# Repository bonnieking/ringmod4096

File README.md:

# ringmod4096

Simple and cool audio effects.

Adapted from:

https://www.asciipr0n.com/4096/ringmod/

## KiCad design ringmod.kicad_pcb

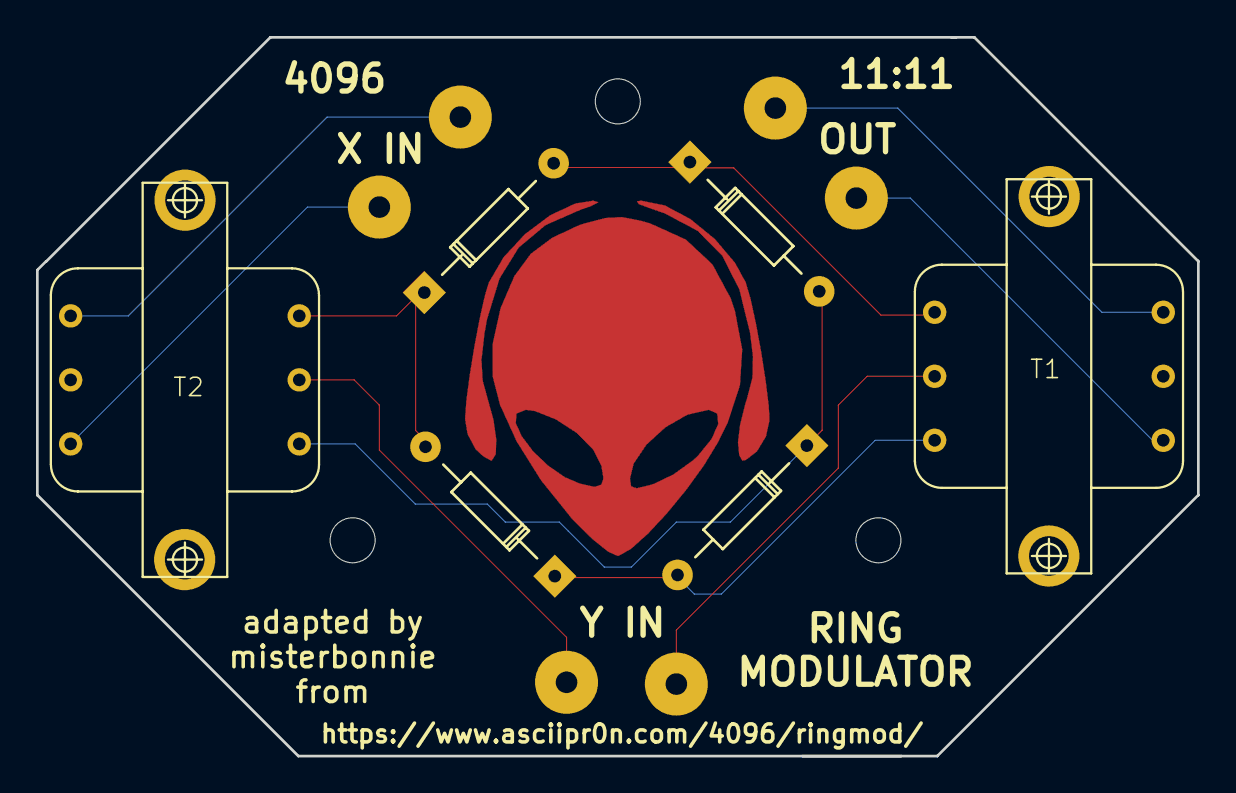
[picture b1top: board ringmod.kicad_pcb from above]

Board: 2 copper layers, 64.5 x 39.9 mm, 12 parts (0 on the bottom side), 10 nets.

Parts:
D1, D2, D3, D4: D; Diode_DO-35_SOD27_Horizontal_RM10
P1, P2, P3, P4, P5, P6: CONN_01X01; SolderWirePad_single_1-2mmDrill
T1, T2: audio_transformer; trafo-xicon-42TM

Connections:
unnamed: D1.1, D3.2, T2.1
unnamed: D1.2, D2.1, T1.3
unnamed: D2.2, D4.1, T2.3
unnamed: D3.1, D4.2, T1.1
unnamed: P1.1, T1.4
unnamed: P2.1, T1.6
unnamed: P3.1, T1.2
unnamed: P4.1, T2.2
unnamed: P5.1, T2.6
unnamed: P6.1, T2.4

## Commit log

2016-06-02 fix the transformer footprint. also all the diodes were BACKWARDS :(
2016-07-24 fix schematic and enlarge mechanical holes for the transformers
2017-01-01 bigger mechanical pads for transformers, move tracks
